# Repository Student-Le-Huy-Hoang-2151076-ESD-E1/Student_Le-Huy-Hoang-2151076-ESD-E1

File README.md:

# Student_Le-Huy-Hoang-2151076-ESD-E1

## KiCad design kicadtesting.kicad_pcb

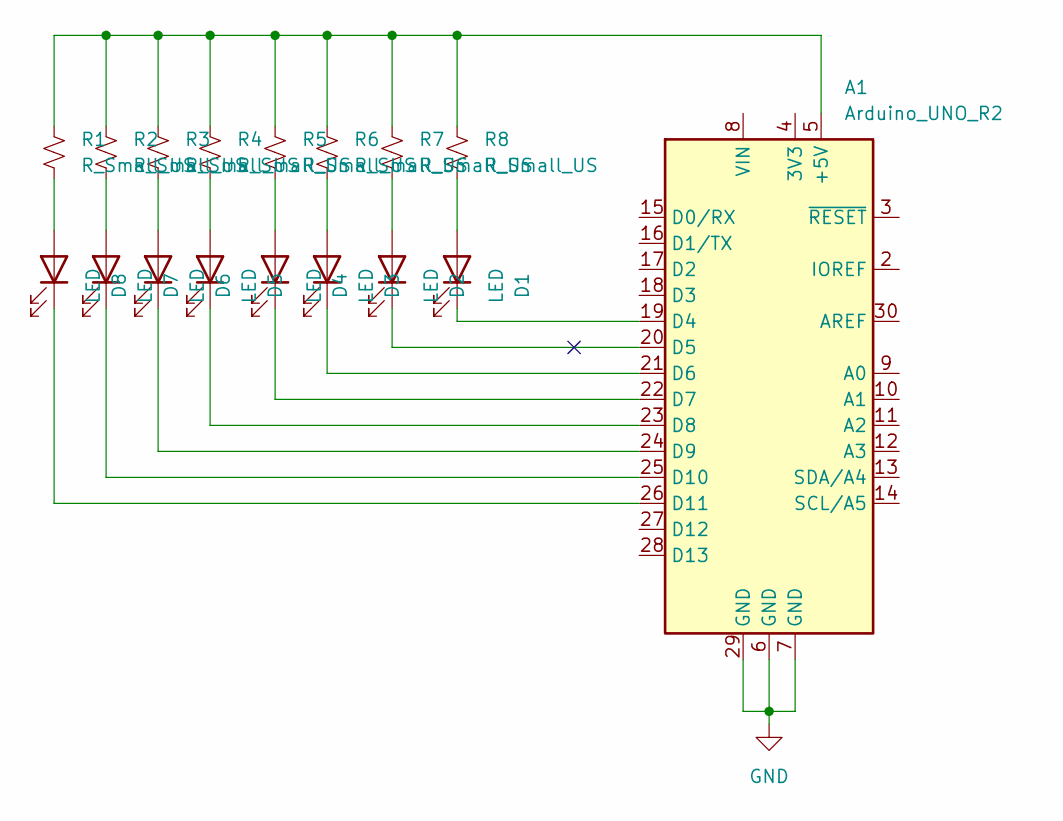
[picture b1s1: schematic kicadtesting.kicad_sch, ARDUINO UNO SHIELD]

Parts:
A1: Arduino_UNO_R2
D1, D2, D3, D4, D5, D6, D7, D8: LED; LED_0805_2012Metric
R1, R2, R3, R4, R5, R6, R7, R8: R_Small_US; R_0603_1608Metric

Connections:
GND: A1.6 (GND), A1.7 (GND), A1.29 (GND)
unnamed: A1.5 (+5V), R1.1, R2.1, R3.1, R4.1, R5.1, R6.1, R7.1, R8.1
unnamed: A1.19 (D4), D1.1 (K)
unnamed: A1.20 (D5), D2.1 (K)
unnamed: A1.21 (D6), D3.1 (K)
unnamed: A1.22 (D7), D4.1 (K)
unnamed: A1.23 (D8), D5.1 (K)
unnamed: A1.24 (D9), D6.1 (K)
unnamed: A1.25 (D10), D7.1 (K)
unnamed: A1.26 (D11), D8.1 (K)
unnamed: D1.2 (A), R8.2
unnamed: D2.2 (A), R7.2
unnamed: D3.2 (A), R6.2
unnamed: D4.2 (A), R5.2
unnamed: D5.2 (A), R4.2
unnamed: D6.2 (A), R3.2
unnamed: D7.2 (A), R2.2
unnamed: D8.2 (A), R1.2

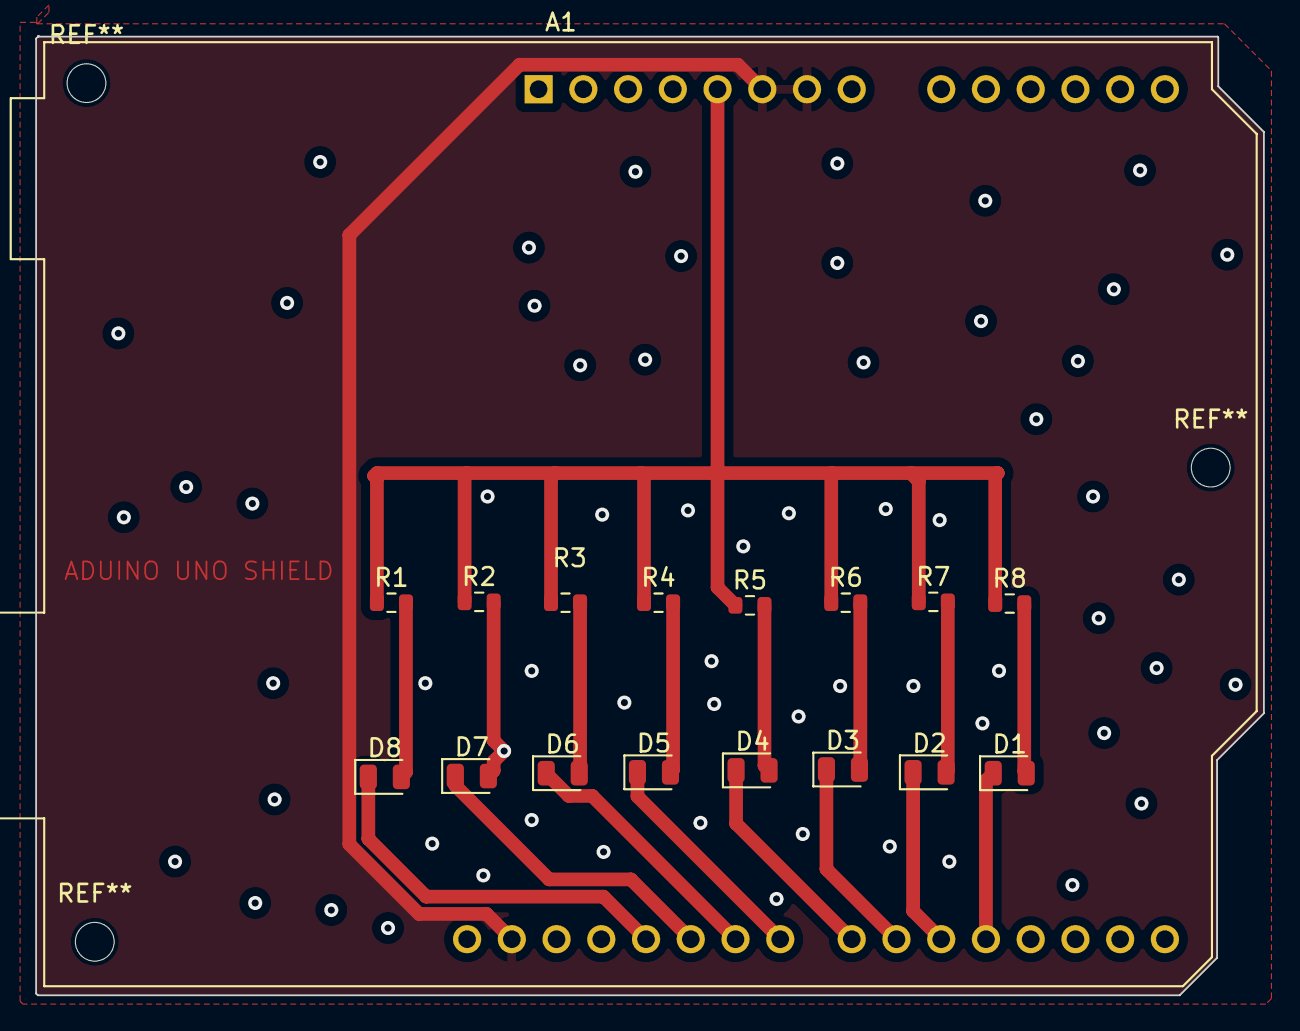
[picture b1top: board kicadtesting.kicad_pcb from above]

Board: 2 copper layers, 69.7 x 54.5 mm, 17 parts (0 on the bottom side), 18 nets.

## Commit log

2024-01-17 Create picture PCB
